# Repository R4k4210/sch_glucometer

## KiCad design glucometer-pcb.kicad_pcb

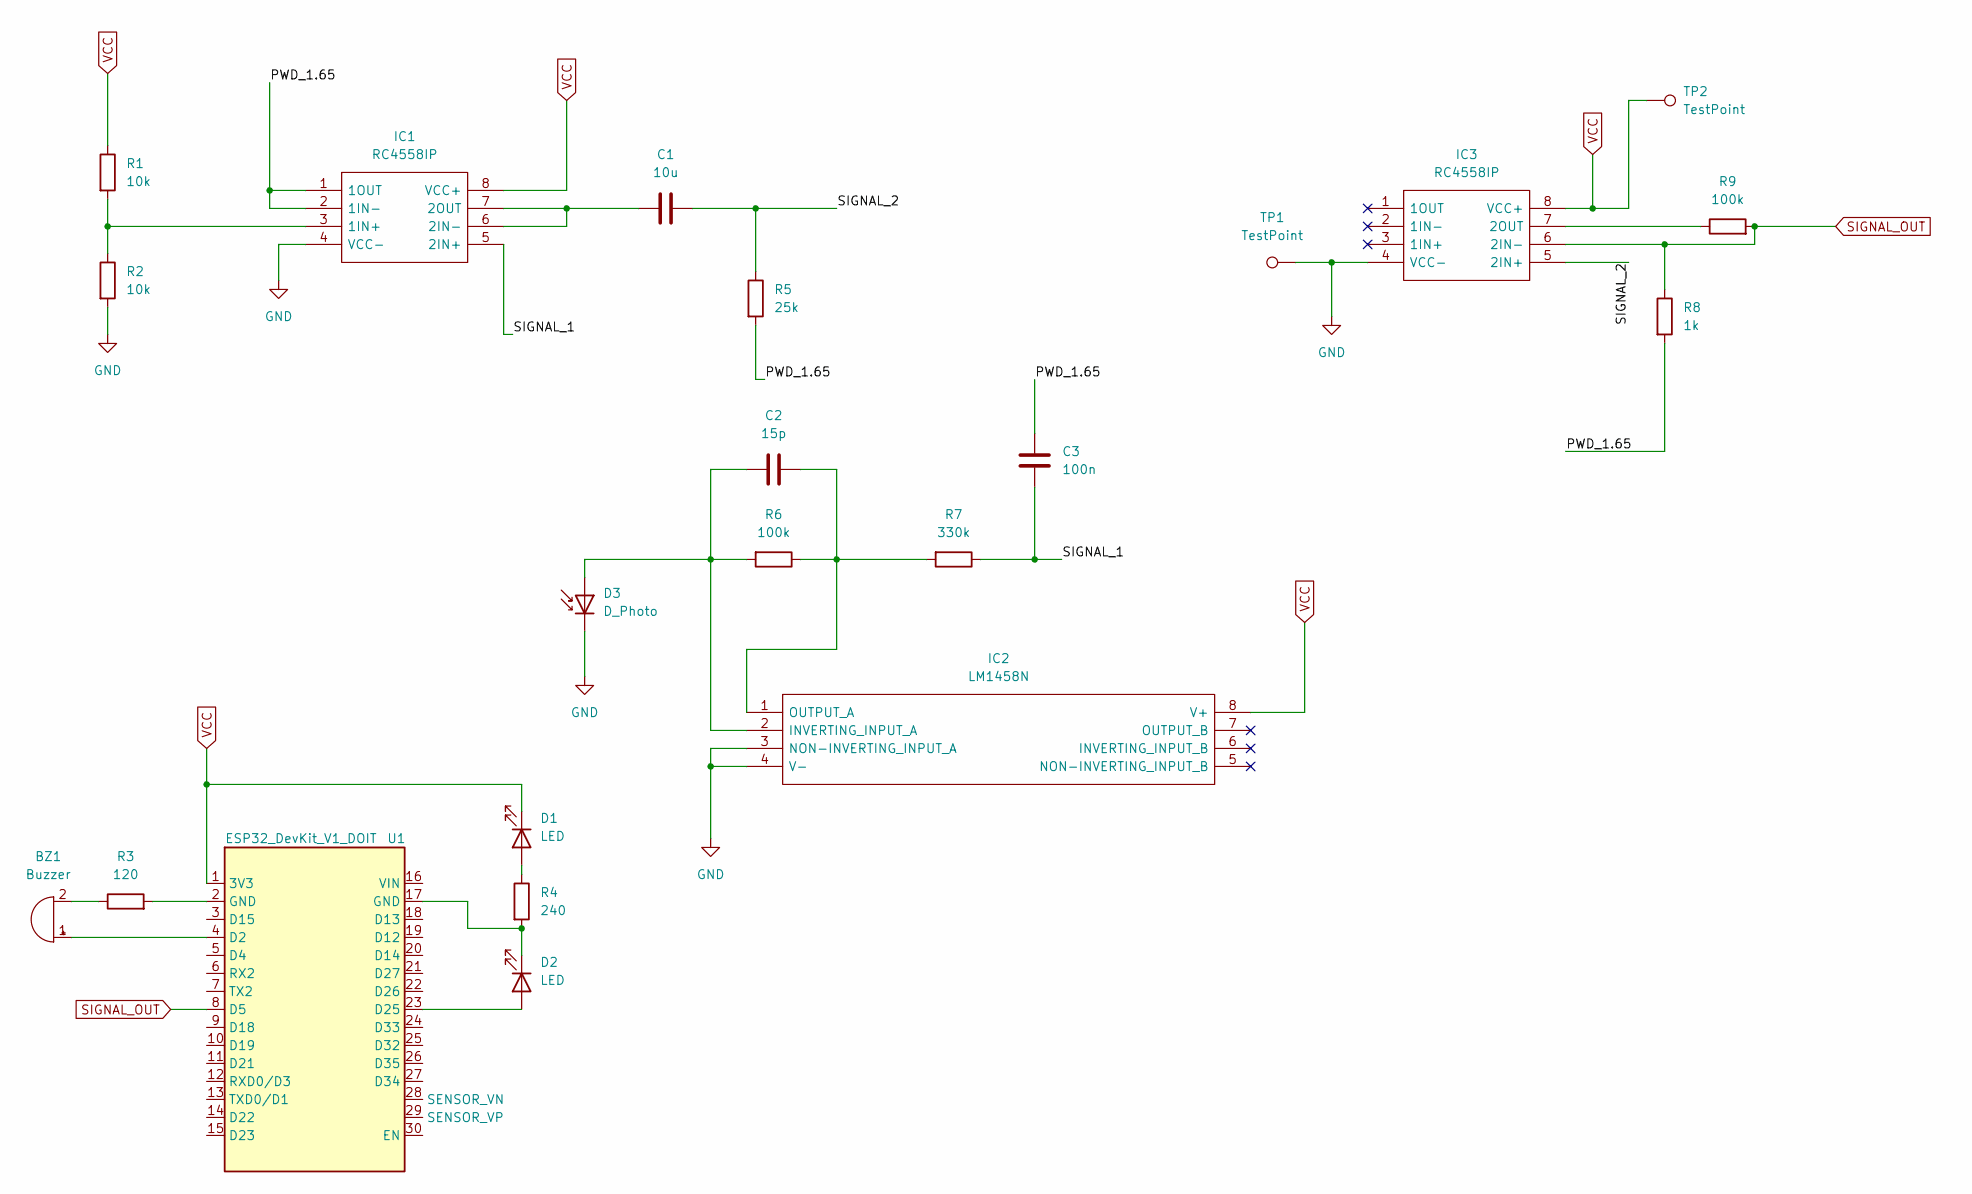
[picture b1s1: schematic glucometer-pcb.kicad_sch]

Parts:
BZ1: Buzzer; MagneticBuzzer_Kingstate_KCG0601
C1: 10u; CP_Radial_Tantal_D7.0mm_P5.00mm
C2: 15p; CP_Radial_D8.0mm_P3.80mm
C3: 100n; CP_Radial_Tantal_D7.0mm_P5.00mm
D1: LED; LED_D3.0mm_Clear
D2: LED; LED_D3.0mm_FlatTop
D3: D_Photo; LED_2010_5025Metric
IC1, IC3: RC4558IP; DIP794W53P254L959H508Q8N; Manufacturer_Part_Number RC4558IP; Mouser Part Number 595-RC4558IP
IC2: LM1458N; MC1458N; Manufacturer_Part_Number LM1458N; Mouser Part Number 926-LM1458N
R1, R2: 10k; R_Axial_DIN0204_L3.6mm_D1.6mm_P7.62mm_Horizontal
R3: 120; R_Axial_DIN0204_L3.6mm_D1.6mm_P7.62mm_Horizontal
R4: 240; R_Axial_DIN0204_L3.6mm_D1.6mm_P7.62mm_Horizontal
R5: 25k; R_Axial_DIN0204_L3.6mm_D1.6mm_P7.62mm_Horizontal
R6, R9: 100k; R_Axial_DIN0204_L3.6mm_D1.6mm_P7.62mm_Horizontal
R7: 330k; R_Axial_DIN0204_L3.6mm_D1.6mm_P7.62mm_Horizontal
R8: 1k; R_Axial_DIN0204_L3.6mm_D1.6mm_P7.62mm_Horizontal
TP1, TP2: TestPoint; TestPoint_Keystone_5015_Micro-Minature
U1: ESP32_DevKit_V1_DOIT; esp32_devkit_v1_doit

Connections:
/PWD_1.65: C3.2, IC1.1 (1OUT), IC1.2 (1IN-), R5.2, R8.2
/SIGNAL_1: C3.1, IC1.5 (2IN+), R7.1
/SIGNAL_2: C1.2, IC3.5 (2IN+), R5.1
GND: D3.1 (K), IC1.4 (VCC-), IC2.3 (NON-INVERTING_INPUT_A), IC2.4 (V-), IC3.4 (VCC-), R2.2, TP1.1
unnamed: BZ1.1 (-), U1.4 (D2)
unnamed: BZ1.2 (+), R3.1
unnamed: C1.1, IC1.6 (2IN-), IC1.7 (2OUT)
unnamed: C2.1, D3.2 (A), IC2.2 (INVERTING_INPUT_A), R6.2
unnamed: C2.2, IC2.1 (OUTPUT_A), R6.1, R7.2
unnamed: D1.2 (A), R4.1
unnamed: D2.1 (K), R4.2, U1.17 (GND)
unnamed: D2.2 (A), U1.23 (D25)
unnamed: IC1.3 (1IN+), R1.2, R2.1
unnamed: IC3.7 (2OUT), R9.1
unnamed: R3.2, U1.2 (GND)
SIGNAL_OUT: IC3.6 (2IN-), R8.1, R9.2, U1.8 (D5)
VCC: D1.1 (K), IC1.8 (VCC+), IC2.8 (V+), IC3.8 (VCC+), R1.1, TP2.1, U1.1 (3V3)

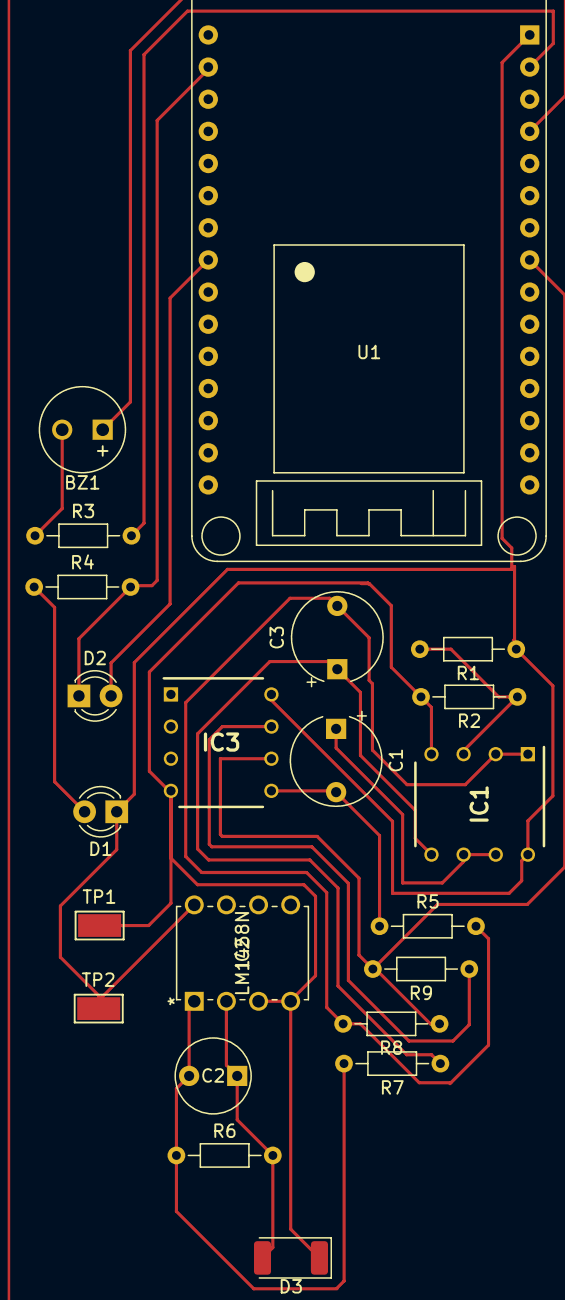
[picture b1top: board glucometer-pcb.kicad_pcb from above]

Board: 2 copper layers, 22 parts (0 on the bottom side), 17 nets.

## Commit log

2022-04-20 files added
2022-04-23 pcb backup
2022-04-24 prototype PCB
2022-04-24 last update pcb

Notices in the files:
parts and their libraries:
Copyright 2021 Accelerated Designs. All rights reserved.
